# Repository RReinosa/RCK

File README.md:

# RCK

### Introduction
----
**Reinosa Custom Keyboard (RCK)** is an open source project dedicated to creating a complete guide on how to create your own custom keyboard from scratch.

In the following sections, we will discuss the step-by-step, hardware/software recommendations and the methodology used for the success of this project.

### Layout design (optional)
----
The first step in creating your own custom mechanical keyboard is whether you want to use an existing keyboard layout (which will make it easier to find the necessary parts) or whether you want to customise the keyboard layout entirely.

In this project, the decision has been made to custom design the layout. The layout is a personal decision and I invite you to spend a lot of time designing the keyboard that best suits you.

In this case, we have used the online tool http://www.keyboard-layout-editor.com/#/ which will allow us to get a first idea of the design of our layout. There are different tools to fulfil this function such as Adobe Illustrator or CorelDRAW.

The end result of our first approximation of the final design will be this:

In the layout folder, you will find the *.json* used for the design of this layout.

### Version control and release
----
Version 1.0
Under development.

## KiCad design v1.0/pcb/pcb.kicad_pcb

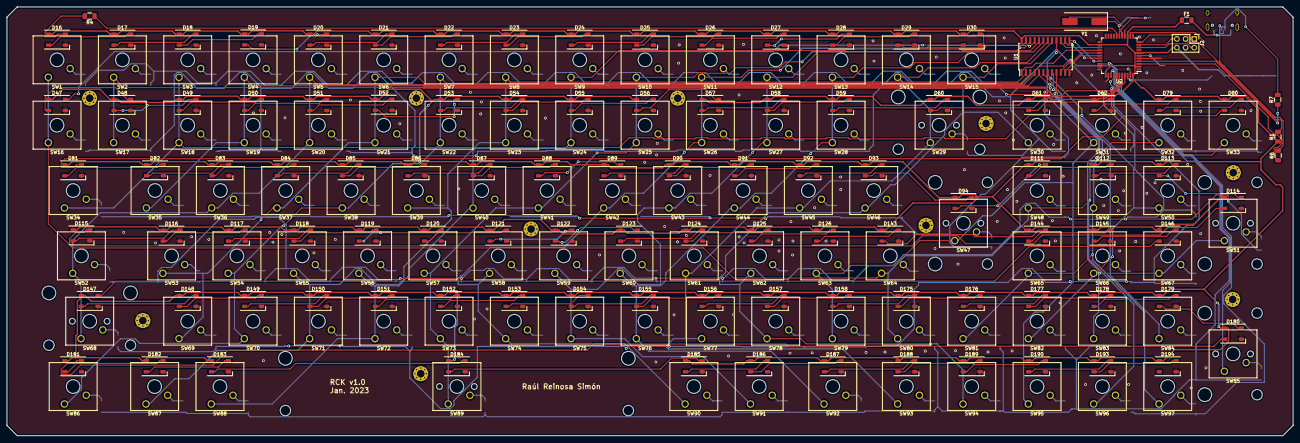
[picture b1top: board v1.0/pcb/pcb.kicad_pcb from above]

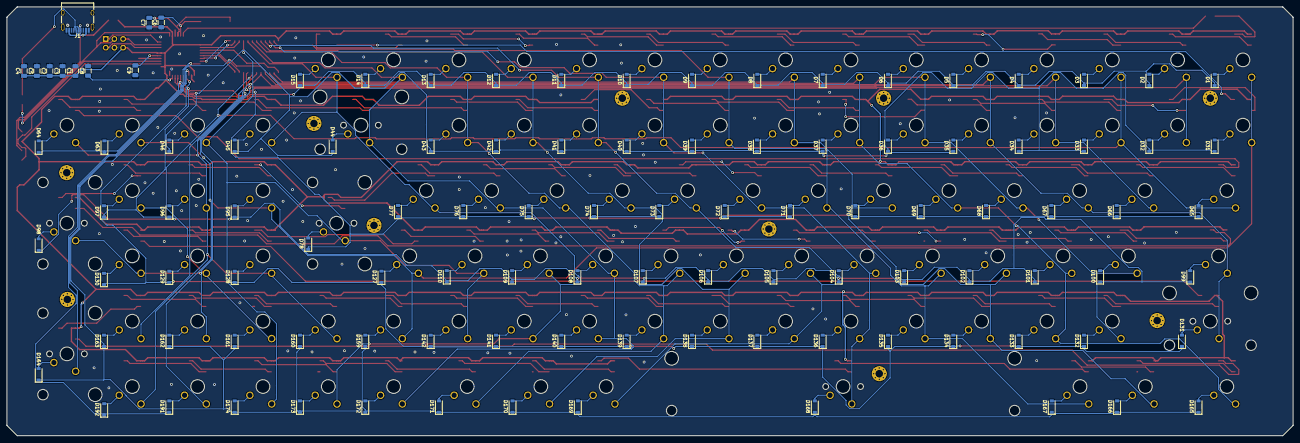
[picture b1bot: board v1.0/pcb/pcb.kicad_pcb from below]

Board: 2 copper layers, 375.0 x 125.0 mm, 320 parts (107 on the bottom side), 239 nets.

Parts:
C1, C2, C3, C5, C8: 0.1uF; C_1206_3216Metric
C4: 10uF; C_1206_3216Metric
C6, C7: 22pF; C_1206_3216Metric
C9: 1uF; C_1206_3216Metric
D1, D2, D3, D4, D5, D6, D7, D8, D9, D10, D11, D12, D13, D14, D15, D31, D32, D33, D34, D35, D36, D37, D38, D39, D40, D41, D42, D43, D44, D45, D46, D63, D64, D65, D66, D67, D68, D69, D70, D71, D72, D73, D74, D75, D76, D77, D78, D95, D96, D97, D98, D99, D100, D101, D102, D103, D104, D105, D106, D107, D108, D109, D110, D127, D128, D129, D130, D131, D132, D133, D134, D135, D136, D137, D138, D139, D140, D141, D142, D159, D160, D161, D162, D163, D164, D165, D166, D167, D168, D169, D170, D171, D172, D173, D174, D191, D192: 1N4148W; D_SOD-123
D16, D17, D18, D19, D20, D21, D22, D23, D24, D25, D26, D27, D28, D29, D30, D47, D48, D49, D50, D51, D52, D53, D54, D55, D56, D57, D58, D59, D60, D61, D62, D79, D80, D81, D82, D83, D84, D85, D86, D87, D88, D89, D90, D91, D92, D93, D94, D111, D112, D113, D114, D115, D116, D117, D118, D119, D120, D121, D122, D123, D124, D125, D126, D143, D144, D145, D146, D147, D148, D149, D150, D151, D152, D153, D154, D155, D156, D157, D158, D175, D176, D177, D178, D179, D180, D181, D182, D183, D184, D185, D186, D187, D188, D189, D190, D193, D194: SK6812; LED_SK6812_PLCC4_5.0x5.0mm_P3.2mm
F1: 500mA; Fuse_1206_3216Metric
H1, H2, H3, H4, H5, H6, H7, H8, H9, H10: MountingHole_Pad; MountingHole_2.2mm_M2_Pad_Via
J1: USB_C_Receptacle_USB2.0; USB_C_Receptacle_HRO_TYPE-C-31-M-12
J2: ISP; PinHeader_2x03_P2.54mm_Vertical
R1: 10k; R_1206_3216Metric
R4: 330; R_1206_3216Metric
R6, R7: 22; R_1206_3216Metric
SW1, SW2, SW3, SW4, SW5, SW6, SW7, SW8, SW9, SW10, SW11, SW12, SW13, SW14, SW15, SW16, SW17, SW18, SW19, SW20, SW21, SW22, SW23, SW24, SW25, SW26, SW27, SW28, SW30, SW31, SW32, SW33, SW35, SW36, SW37, SW38, SW39, SW40, SW41, SW42, SW43, SW44, SW45, SW46, SW48, SW49, SW50, SW53, SW54, SW55, SW56, SW57, SW58, SW59, SW60, SW61, SW62, SW63, SW64, SW65, SW66, SW67, SW69, SW70, SW71, SW72, SW73, SW74, SW75, SW76, SW77, SW78, SW79, SW80, SW81, SW82, SW83, SW84, SW87, SW88, SW90, SW91, SW93, SW94, SW95, SW96, SW97: SW_Push; SW_Cherry_MX_1.00u_Plate
SW29, SW68: SW_Push; SW_Cherry_MX_2.00u_PCB
SW34, SW86: SW_Push; SW_Cherry_MX_1.50u_Plate
SW47: SW_Push; SW_Cherry_MX_ISOEnter_PCB
SW51, SW85: SW_Push; SW_Cherry_MX_2.00u_Vertical_PCB
SW52: SW_Push; SW_Cherry_MX_1.75u_Plate
SW89: SW_Push; SW_Cherry_MX_6.25u_PCB
SW92: SW_Push; SW_Cherry_MX_1.25u_Plate
U1: CD74HC4067M; SOIC-24W_7.5x15.4mm_P1.27mm
U2: ATmega32U4-AU; TQFP-44_10x10mm_P0.8mm
Y1: 16MHz; Crystal_SMD_HC49-SD

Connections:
+5V: C1.1, C2.1, C3.1, C4.1, C5.1, D16.3, D17.3, D18.3, D19.3, D20.3, D21.3, D22.3, D23.3, D24.3, D25.3, D26.3, D27.3, D28.3, D29.3, D30.3, D47.3, D48.3, D49.3, D50.3, D51.3, D52.3, D53.3, D54.3, D55.3, D56.3, D57.3, D58.3, D59.3, D60.3, D61.3, D62.3, D79.3, D80.3, D81.3, D82.3, D83.3, D84.3, D85.3, D86.3, D87.3, D88.3, D89.3, D90.3, D91.3, D92.3, D93.3, D94.3, D111.3, D112.3, D113.3, D114.3, D115.3, D116.3, D117.3, D118.3, D119.3, D120.3, D121.3, D122.3, D123.3, D124.3, D125.3, D126.3, D143.3, D144.3, D145.3, D146.3, D147.3, D148.3, D149.3, D150.3, D151.3, D152.3, D153.3, D154.3, D155.3, D156.3, D157.3, D158.3, D175.3, D176.3, D177.3, D178.3, D179.3, D180.3, D181.3, D182.3, D183.3, D184.3, D185.3, D186.3, D187.3, D188.3, D189.3, D190.3, D193.3, D194.3, F1.1, J2.6, R1.1, U1.24, U2.2, U2.7, U2.14, U2.24, U2.34, U2.44
C0: SW1.1, SW16.1, SW32.1, SW48.1, SW64.1, SW80.1, SW96.1, U1.9
C1: SW2.1, SW17.1, SW33.1, SW49.1, SW65.1, SW81.1, SW97.1, U1.8
C2: SW3.1, SW18.1, SW34.1, SW50.1, SW66.1, SW82.1, U1.7
C3: SW4.1, SW19.1, SW35.1, SW51.1, SW67.1, SW83.1, U1.6
C4: SW5.1, SW20.1, SW36.1, SW52.1, SW68.1, SW84.1, U1.5
C5: SW6.1, SW21.1, SW37.1, SW53.1, SW69.1, SW85.1, U1.4
C6: SW7.1, SW22.1, SW38.1, SW54.1, SW70.1, SW86.1, U1.3
C7: SW8.1, SW23.1, SW39.1, SW55.1, SW71.1, SW87.1, U1.2
C8: SW9.1, SW24.1, SW40.1, SW56.1, SW72.1, SW88.1, U1.23
C9: SW10.1, SW25.1, SW41.1, SW57.1, SW73.1, SW89.1, U1.22
C10: SW11.1, SW26.1, SW42.1, SW58.1, SW74.1, SW90.1, U1.21
C11: SW12.1, SW27.1, SW43.1, SW59.1, SW75.1, SW91.1, U1.20
C12: SW13.1, SW28.1, SW44.1, SW60.1, SW76.1, SW92.1, U1.19
C13: SW14.1, SW29.1, SW45.1, SW61.1, SW77.1, SW93.1, U1.18
C14: SW15.1, SW30.1, SW46.1, SW62.1, SW78.1, SW94.1, U1.17
C15: SW31.1, SW47.1, SW63.1, SW79.1, SW95.1, U1.16
COM: U1.1, U2.26
D+: R7.1, U2.4
D-: R6.1, U2.3
GND: C1.2, C2.2, C3.2, C4.2, C5.2, C6.1, C7.1, C8.2, C9.1, D16.1, D17.1, D18.1, D19.1, D20.1, D21.1, D22.1, D23.1, D24.1, D25.1, D26.1, D27.1, D28.1, D29.1, D30.1, D47.1, D48.1, D49.1, D50.1, D51.1, D52.1, D53.1, D54.1, D55.1, D56.1, D57.1, D58.1, D59.1, D60.1, D61.1, D62.1, D79.1, D80.1, D81.1, D82.1, D83.1, D84.1, D85.1, D86.1, D87.1, D88.1, D89.1, D90.1, D91.1, D92.1, D93.1, D94.1, D111.1, D112.1, D113.1, D114.1, D115.1, D116.1, D117.1, D118.1, D119.1, D120.1, D121.1, D122.1, D123.1, D124.1, D125.1, D126.1, D143.1, D144.1, D145.1, D146.1, D147.1, D148.1, D149.1, D150.1, D151.1, D152.1, D153.1, D154.1, D155.1, D156.1, D157.1, D158.1, D175.1, D176.1, D177.1, D178.1, D179.1, D180.1, D181.1, D182.1, D183.1, D184.1, D185.1, D186.1, D187.1, D188.1, D189.1, D190.1, D193.1, D194.1, H1.1, H2.1, H3.1, H4.1, H5.1, H6.1, H7.1, H8.1, H9.1, H10.1, J1.A1, J1.A12, J1.B1, J1.B12, J1.S1, J2.4, U1.12, U2.5, U2.15, U2.23, U2.33, U2.35, U2.43
LED0: R4.1, U2.18
LED1: D30.4, D47.2
LED2: D62.4, D79.2
LED3: D94.4, D111.2
LED4: D126.4, D143.2
LED5: D158.4, D175.2
LED6: D190.4, D193.2
MISO: J2.1, U2.11
MOSI: J2.5, U2.10
unnamed: C6.2, U2.17, Y1.1
unnamed: C7.2, U2.16, Y1.2
unnamed: C8.1, U2.42
unnamed: C9.2, U2.6
unnamed: D1.2, SW1.2
unnamed: D2.2, SW2.2
unnamed: D3.2, SW3.2
unnamed: D4.2, SW4.2
unnamed: D5.2, SW5.2
unnamed: D6.2, SW6.2
unnamed: D7.2, SW7.2
unnamed: D8.2, SW8.2
unnamed: D9.2, SW9.2
unnamed: D10.2, SW10.2
unnamed: D11.2, SW11.2
unnamed: D12.2, SW12.2
unnamed: D13.2, SW13.2
unnamed: D14.2, SW14.2
unnamed: D15.2, SW15.2
unnamed: D16.2, R4.2
unnamed: D16.4, D17.2
unnamed: D17.4, D18.2
unnamed: D18.4, D19.2
unnamed: D19.4, D20.2
unnamed: D20.4, D21.2
unnamed: D21.4, D22.2
unnamed: D22.4, D23.2
unnamed: D23.4, D24.2
unnamed: D24.4, D25.2
unnamed: D25.4, D26.2
unnamed: D26.4, D27.2
unnamed: D27.4, D28.2
unnamed: D28.4, D29.2
unnamed: D29.4, D30.2
unnamed: D31.2, SW16.2
unnamed: D32.2, SW17.2
unnamed: D33.2, SW18.2
unnamed: D34.2, SW19.2
unnamed: D35.2, SW20.2
unnamed: D36.2, SW21.2
unnamed: D37.2, SW22.2
unnamed: D38.2, SW23.2
unnamed: D39.2, SW24.2
unnamed: D40.2, SW25.2
unnamed: D41.2, SW26.2
unnamed: D42.2, SW27.2
unnamed: D43.2, SW28.2
unnamed: D44.2, SW29.2
unnamed: D45.2, SW30.2
unnamed: D46.2, SW31.2
unnamed: D47.4, D48.2
unnamed: D48.4, D49.2
unnamed: D49.4, D50.2
unnamed: D50.4, D51.2
unnamed: D51.4, D52.2
unnamed: D52.4, D53.2
unnamed: D53.4, D54.2
unnamed: D54.4, D55.2
unnamed: D55.4, D56.2
unnamed: D56.4, D57.2
unnamed: D57.4, D58.2
unnamed: D58.4, D59.2
unnamed: D59.4, D60.2
unnamed: D60.4, D61.2
unnamed: D61.4, D62.2
unnamed: D63.2, SW32.2
unnamed: D64.2, SW33.2
unnamed: D65.2, SW34.2
unnamed: D66.2, SW35.2
unnamed: D67.2, SW36.2
unnamed: D68.2, SW37.2
unnamed: D69.2, SW38.2
unnamed: D70.2, SW39.2
unnamed: D71.2, SW40.2
unnamed: D72.2, SW41.2
unnamed: D73.2, SW42.2
unnamed: D74.2, SW43.2
unnamed: D75.2, SW44.2
unnamed: D76.2, SW45.2
unnamed: D77.2, SW46.2
unnamed: D78.2, SW47.2
unnamed: D79.4, D80.2
unnamed: D80.4, D81.2
unnamed: D81.4, D82.2
unnamed: D82.4, D83.2
unnamed: D83.4, D84.2
unnamed: D84.4, D85.2
unnamed: D85.4, D86.2
unnamed: D86.4, D87.2
unnamed: D87.4, D88.2
unnamed: D88.4, D89.2
unnamed: D89.4, D90.2
unnamed: D90.4, D91.2
unnamed: D91.4, D92.2
unnamed: D92.4, D93.2
unnamed: D93.4, D94.2
unnamed: D95.2, SW48.2
unnamed: D96.2, SW49.2
unnamed: D97.2, SW50.2
unnamed: D98.2, SW51.2
unnamed: D99.2, SW52.2
unnamed: D100.2, SW53.2
unnamed: D101.2, SW54.2
unnamed: D102.2, SW55.2
unnamed: D103.2, SW56.2
unnamed: D104.2, SW57.2
unnamed: D105.2, SW58.2
unnamed: D106.2, SW59.2
unnamed: D107.2, SW60.2
unnamed: D108.2, SW61.2
unnamed: D109.2, SW62.2
unnamed: D110.2, SW63.2
unnamed: D111.4, D112.2
unnamed: D112.4, D113.2
unnamed: D113.4, D114.2
unnamed: D114.4, D115.2
unnamed: D115.4, D116.2
unnamed: D116.4, D117.2
unnamed: D117.4, D118.2
unnamed: D118.4, D119.2
unnamed: D119.4, D120.2
unnamed: D120.4, D121.2
unnamed: D121.4, D122.2
unnamed: D122.4, D123.2
unnamed: D123.4, D124.2
unnamed: D124.4, D125.2
unnamed: D125.4, D126.2
unnamed: D127.2, SW64.2
unnamed: D128.2, SW65.2
unnamed: D129.2, SW66.2
unnamed: D130.2, SW67.2
unnamed: D131.2, SW68.2
unnamed: D132.2, SW69.2
unnamed: D133.2, SW70.2
unnamed: D134.2, SW71.2
unnamed: D135.2, SW72.2
unnamed: D136.2, SW73.2
unnamed: D137.2, SW74.2
unnamed: D138.2, SW75.2
unnamed: D139.2, SW76.2
unnamed: D140.2, SW77.2
unnamed: D141.2, SW78.2
unnamed: D142.2, SW79.2
unnamed: D143.4, D144.2
unnamed: D144.4, D145.2
unnamed: D145.4, D146.2
unnamed: D146.4, D147.2
unnamed: D147.4, D148.2
unnamed: D148.4, D149.2
unnamed: D149.4, D150.2
unnamed: D150.4, D151.2
unnamed: D151.4, D152.2
unnamed: D152.4, D153.2
unnamed: D153.4, D154.2
unnamed: D154.4, D155.2
unnamed: D155.4, D156.2
unnamed: D156.4, D157.2
unnamed: D157.4, D158.2
unnamed: D159.2, SW80.2
unnamed: D160.2, SW81.2
unnamed: D161.2, SW82.2
unnamed: D162.2, SW83.2
unnamed: D163.2, SW84.2
unnamed: D164.2, SW85.2
unnamed: D165.2, SW86.2
unnamed: D166.2, SW87.2
unnamed: D167.2, SW88.2
unnamed: D168.2, SW89.2
unnamed: D169.2, SW90.2
unnamed: D170.2, SW91.2
unnamed: D171.2, SW92.2
unnamed: D172.2, SW93.2
unnamed: D173.2, SW94.2
unnamed: D174.2, SW95.2
unnamed: D175.4, D176.2
unnamed: D176.4, D177.2
unnamed: D177.4, D178.2
unnamed: D178.4, D179.2
unnamed: D179.4, D180.2
unnamed: D180.4, D181.2
unnamed: D181.4, D182.2
unnamed: D182.4, D183.2
unnamed: D183.4, D184.2
unnamed: D184.4, D185.2
unnamed: D185.4, D186.2
unnamed: D186.4, D187.2
unnamed: D187.4, D188.2
unnamed: D188.4, D189.2
unnamed: D189.4, D190.2
unnamed: D191.2, SW96.2
unnamed: D192.2, SW97.2
unnamed: D193.4, D194.2
unnamed: F1.2, J1.A4, J1.A9, J1.B4, J1.B9
unnamed: J1.A6, J1.B6, R7.2
unnamed: J1.A7, J1.B7, R6.2
R0: D1.1, D2.1, D3.1, D4.1, D5.1, D6.1, D7.1, D8.1, D9.1, D10.1, D11.1, D12.1, D13.1, D14.1, D15.1, U2.41
R1: D31.1, D32.1, D33.1, D34.1, D35.1, D36.1, D37.1, D38.1, D39.1, D40.1, D41.1, D42.1, D43.1, D44.1, D45.1, D46.1, U2.40
R2: D63.1, D64.1, D65.1, D66.1, D67.1, D68.1, D69.1, D70.1, D71.1, D72.1, D73.1, D74.1, D75.1, D76.1, D77.1, D78.1, U2.39
R3: D95.1, D96.1, D97.1, D98.1, D99.1, D100.1, D101.1, D102.1, D103.1, D104.1, D105.1, D106.1, D107.1, D108.1, D109.1, D110.1, U2.38
R4: D127.1, D128.1, D129.1, D130.1, D131.1, D132.1, D133.1, D134.1, D135.1, D136.1, D137.1, D138.1, D139.1, D140.1, D141.1, D142.1, U2.37
R5: D159.1, D160.1, D161.1, D162.1, D163.1, D164.1, D165.1, D166.1, D167.1, D168.1, D169.1, D170.1, D171.1, D172.1, D173.1, D174.1, U2.36
R6: D191.1, D192.1, U2.31
RST: J2.3, R1.2, U2.13
S0: U1.10, U2.27
S1: U1.11, U2.28
S2: U1.14, U2.29
S3: U1.13, U2.30
SCK: J2.2, U2.9
SE: U1.15, U2.25

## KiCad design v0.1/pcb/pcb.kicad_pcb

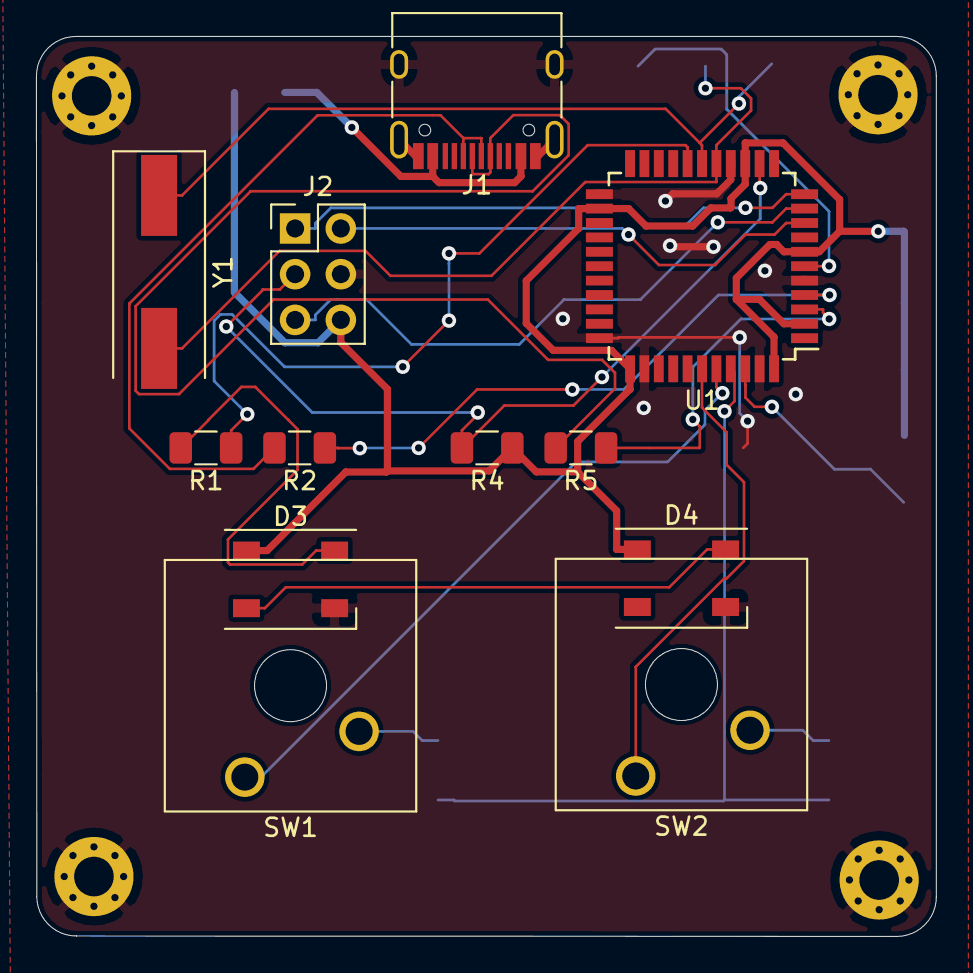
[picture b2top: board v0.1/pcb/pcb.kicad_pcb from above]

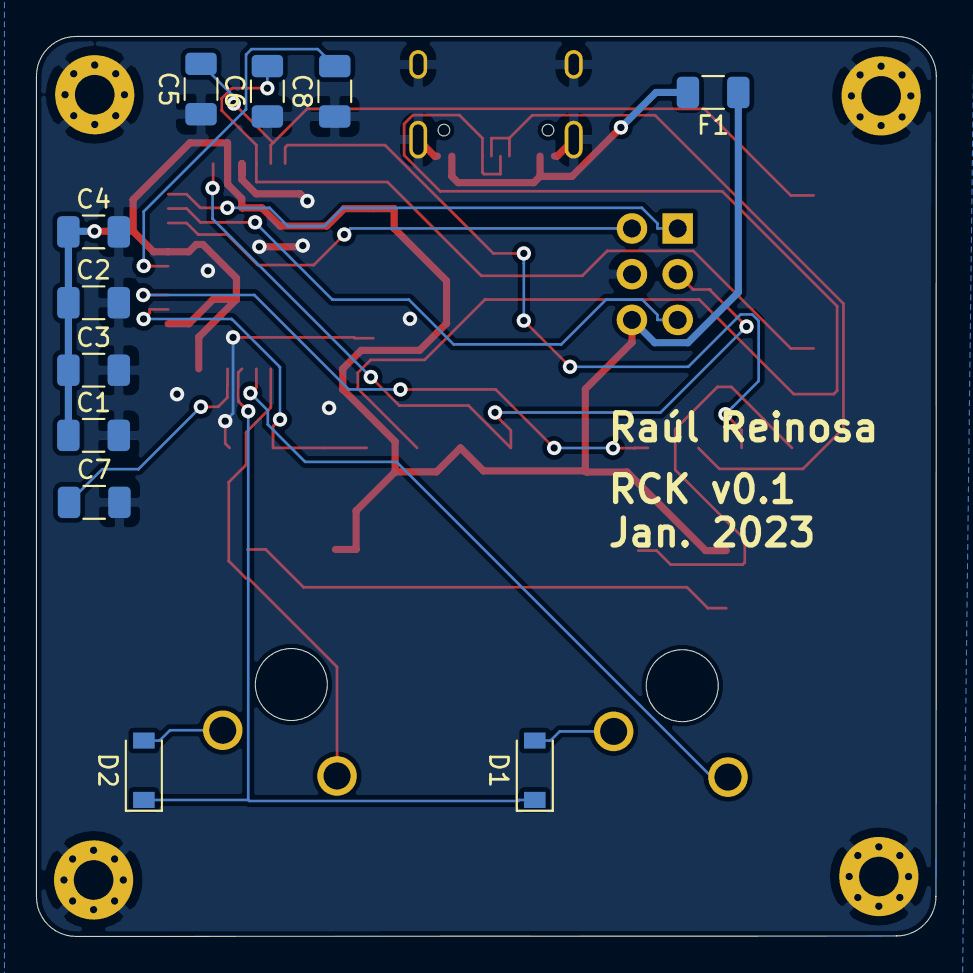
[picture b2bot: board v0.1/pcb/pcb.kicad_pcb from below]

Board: 2 copper layers, 50.0 x 50.0 mm, 27 parts (11 on the bottom side), 23 nets.

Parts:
C1, C2, C3, C7: 0.1uF; C_1206_3216Metric
C4: 10uF; C_1206_3216Metric
C5, C6: 22pF; C_1206_3216Metric
C8: 1uF; C_1206_3216Metric
D1, D2: 1N4148W; D_SOD-123
D3, D4: SK6812; LED_SK6812_PLCC4_5.0x5.0mm_P3.2mm
F1: 500mA; Fuse_1206_3216Metric
H1, H2, H3, H4: MountingHole_Pad; MountingHole_2.2mm_M2_Pad_Via
J1: USB_C_Receptacle_USB2.0; USB_C_Receptacle_HRO_TYPE-C-31-M-12
J2: ISP; PinHeader_2x03_P2.54mm_Vertical
R1: 330; R_1206_3216Metric
R2, R5: 22; R_1206_3216Metric
R4: 10k; R_1206_3216Metric
SW1, SW2: SW_Push; SW_Cherry_MX_1.00u_Plate
U1: ATmega32U4-AU; TQFP-44_10x10mm_P0.8mm
Y1: 16MHz; Crystal_SMD_HC49-SD

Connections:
+5V: C1.1, C2.1, C3.1, C4.1, D3.3, D4.3, F1.1, J2.6, R4.1, U1.2, U1.7, U1.14, U1.24, U1.34, U1.44
C0: SW1.1, U1.40
C1: SW2.1, U1.39
D+: R2.1, U1.4
D-: R5.1, U1.3
GND: C1.2, C2.2, C3.2, C4.2, C5.1, C6.1, C7.2, C8.1, D3.1, D4.1, H1.1, H2.1, H3.1, H4.1, J1.A1, J1.A12, J1.B1, J1.B12, J1.S1, J2.4, U1.5, U1.15, U1.23, U1.33, U1.35, U1.43
LED0: R1.1, U1.18
MISO: J2.1, U1.11
MOSI: J2.5, U1.10
unnamed: C5.2, U1.17, Y1.1
unnamed: C6.2, U1.16, Y1.2
unnamed: C7.1, U1.42
unnamed: C8.2, U1.6
unnamed: D1.2, SW1.2
unnamed: D2.2, SW2.2
unnamed: D3.2, R1.2
unnamed: D3.4, D4.2
unnamed: F1.2, J1.A4, J1.A9, J1.B4, J1.B9
unnamed: J1.A6, J1.B6, R2.2
unnamed: J1.A7, J1.B7, R5.2
R0: D1.1, D2.1, U1.41
RST: J2.3, R4.2, U1.13
SCK: J2.2, U1.9

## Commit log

2023-01-28 layout
2023-01-28 pcb template
2023-01-28 pcb aggregate submodules
2023-01-28 Add footprint libraries
2023-01-28 creating pcb electronic parts
2023-01-28 fix bug switches
2023-01-28 add pcb
2023-01-29 add footprint usbC-2.0
2023-01-29 add usbC kicad configuration
2023-01-29 add matrix switches
2023-01-29 working on pcb
2023-01-30 sch done
2023-01-30 update pcb
2023-01-31 continue working on pcb
2023-02-01 continue with pcb
2023-02-01 maybe first version
2023-02-02 still working on it
2023-02-02 near to finish pcb
2023-02-03 near to have final version pcb ;)
2023-02-07 add test pcb
2023-02-07 maybe pcb done
2023-02-07 update budget
2023-02-08 update proyects
2023-02-08 update progress
2023-02-09 starting with software
2023-02-10 first steps with software
2023-02-12 update software status
2023-02-12 added keyAliases software
2023-02-16 plate
2023-02-21 software changes
2023-02-21 software first version done
2023-02-23 updating software features
2023-02-23 create new gerbers files
2023-02-23 add pdf schema file
2023-02-28 fix software issues
2023-03-03 plate done
2023-03-03 updating software
2023-03-10 working on plate and software v1.0
2023-10-01 fix: Added last 3d shapes
